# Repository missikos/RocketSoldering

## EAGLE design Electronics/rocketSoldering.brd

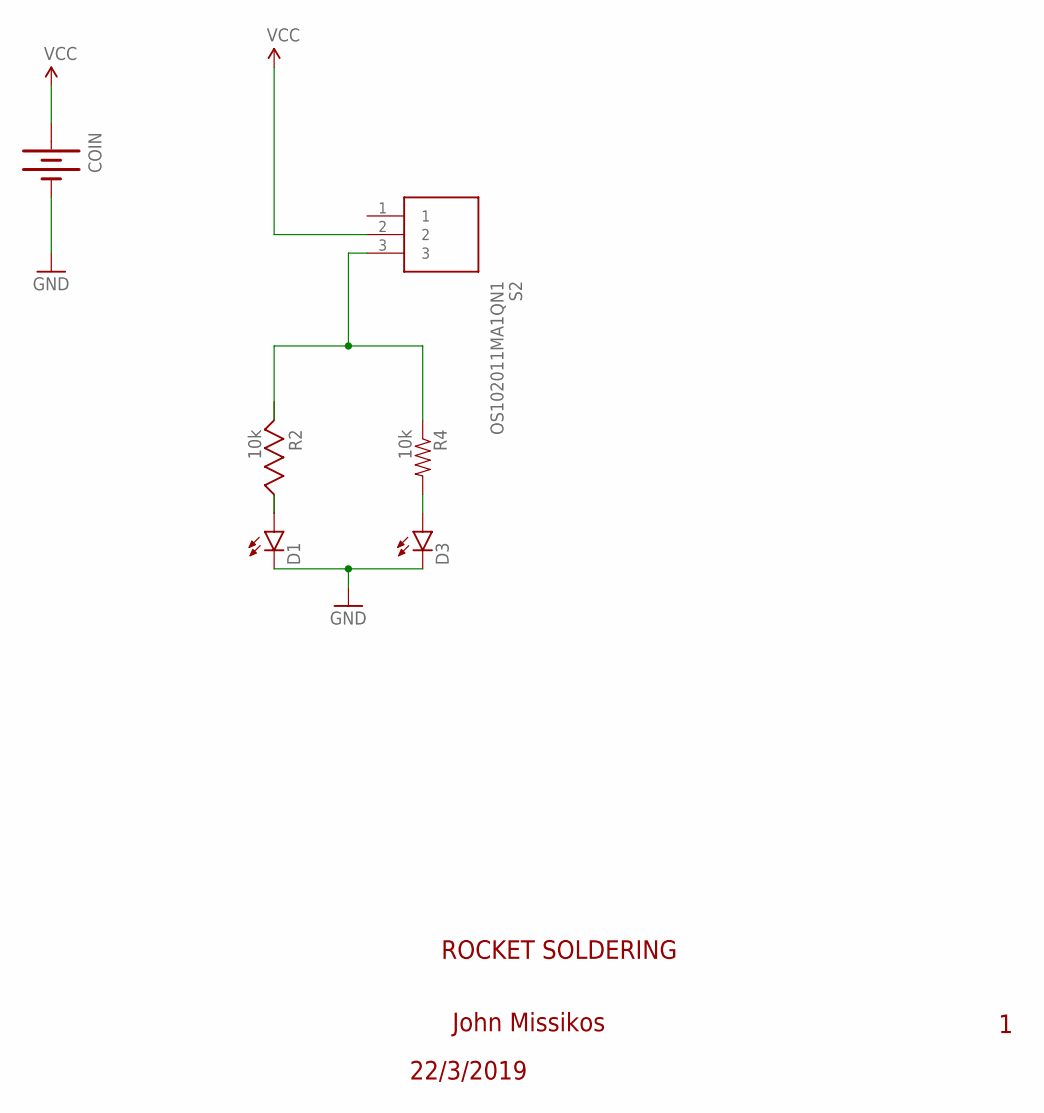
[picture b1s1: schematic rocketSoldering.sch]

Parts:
COIN: BATTERY_20MM20PTH; BATTCOM_20MM_PTH
D1, D3: LED5MM
R2: 10k; CRCW12060000Z0EA_RESC3216X65
R4: 10k; AXIAL-0.3
S2: OS102011MA1QN1

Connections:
GND: COIN.2 (-), D1.K (C), D3.K (C)
unnamed: D1.A, R2.2
unnamed: R2.1, R4.P$1 (1), S2.3
unnamed: D3.A, R4.P$2 (2)
VCC: COIN.1 (+), S2.2

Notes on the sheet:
ROCKET SOLDERING
John Missikos
22/3/2019

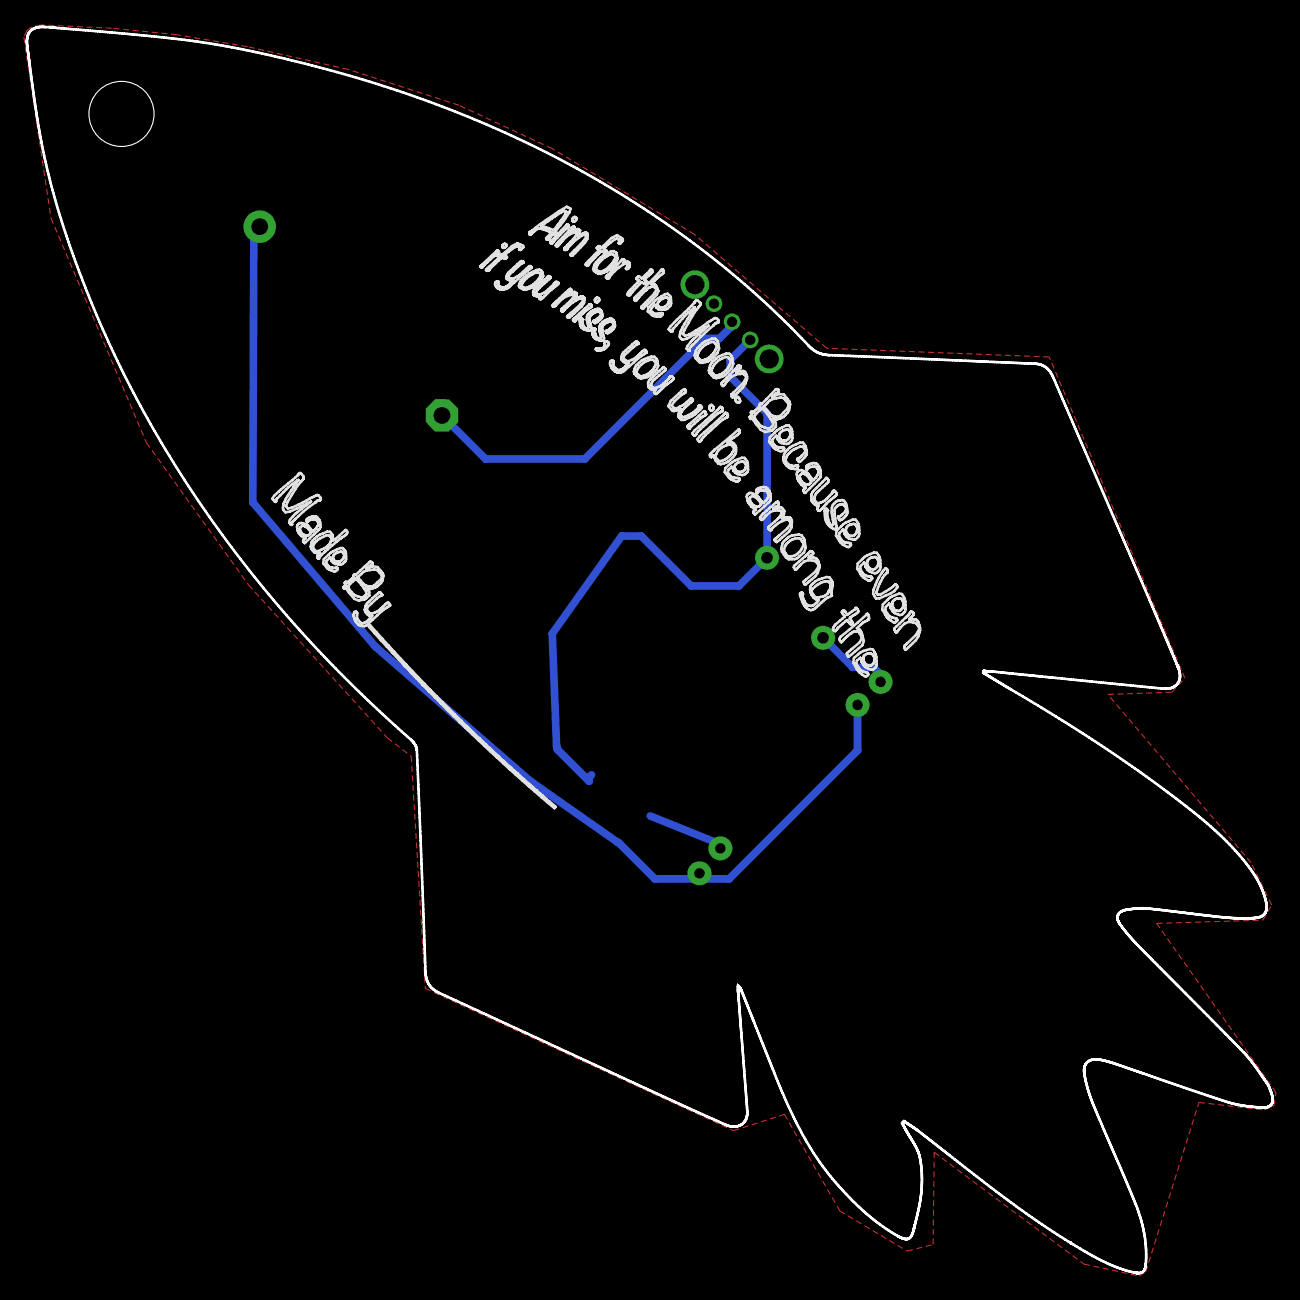
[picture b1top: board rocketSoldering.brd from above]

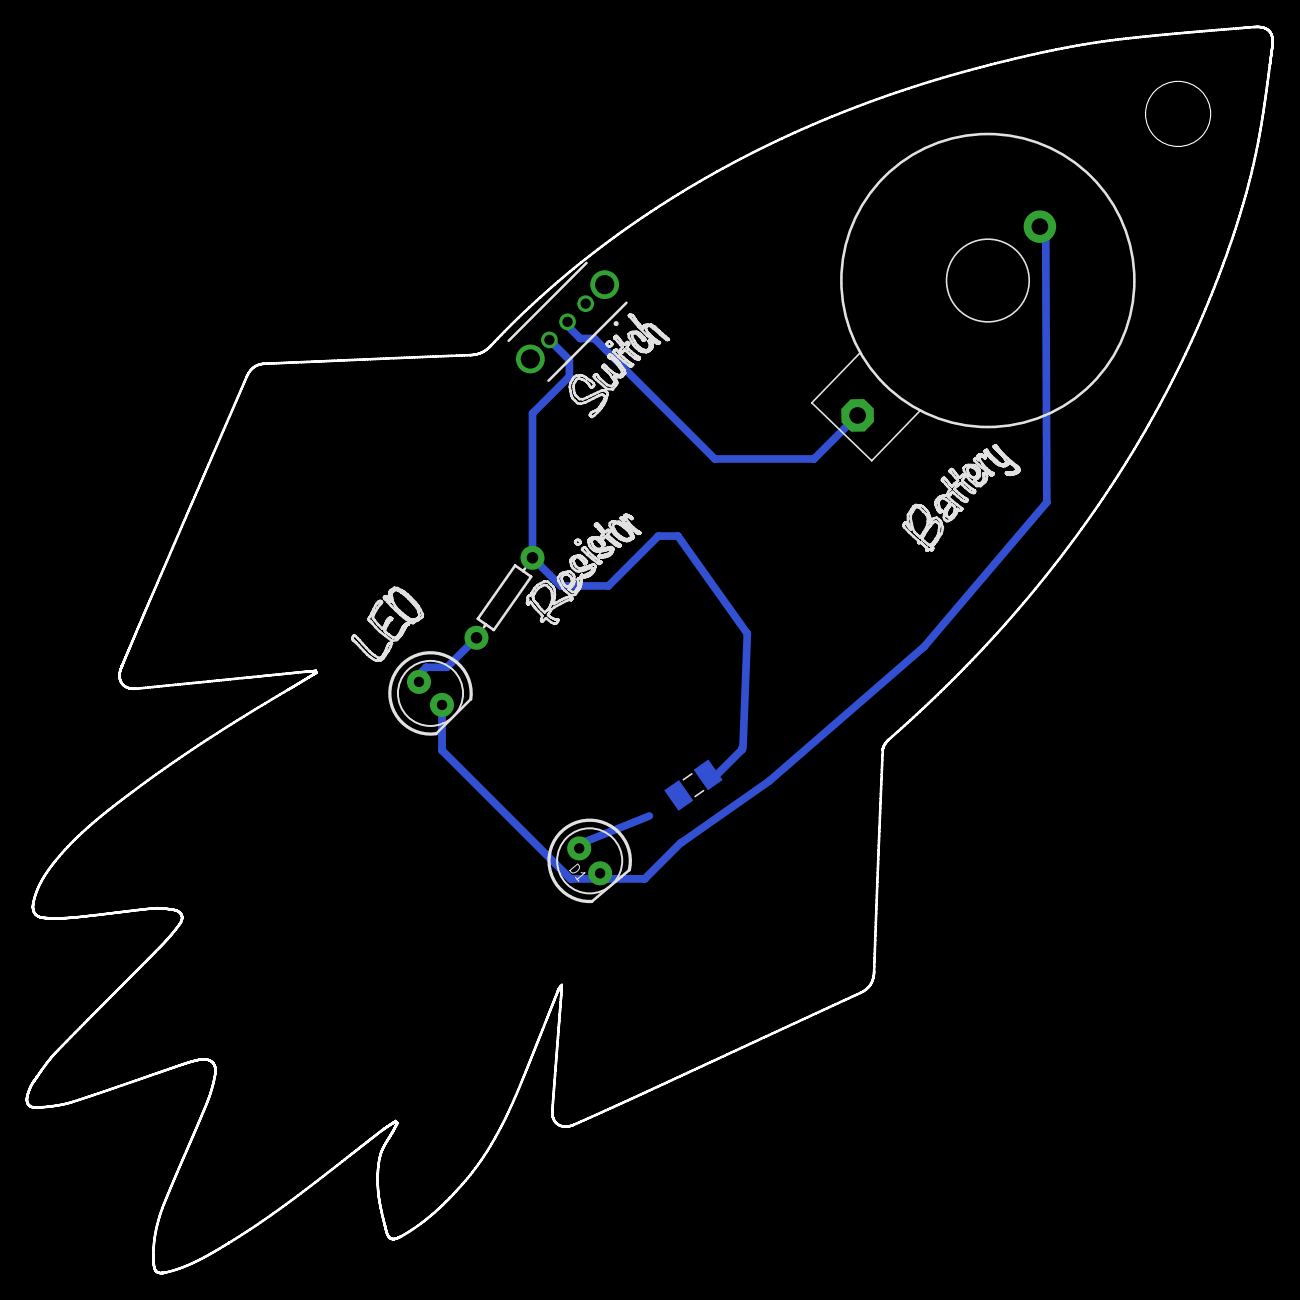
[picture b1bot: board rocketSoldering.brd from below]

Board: 2 copper layers, 97.3 x 97.3 mm, 6 parts (6 on the bottom side), 5 nets.

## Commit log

2019-04-11 Initial
2019-04-11 Added marketing images
2019-12-19 Changed resistor to SMD

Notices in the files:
parts and their libraries:
SparkFun-LED: Licensing: Creative Commons ShareAlike 4.0 International - https://creativecommons.org/licenses/by-sa/4.0
